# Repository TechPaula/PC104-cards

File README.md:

# PC104-cards

This is a place I will be putting various PCBs to go ontop of my PC104+ minicomputer.
No warranty for anything here, I add stuff as/when I feel like it and I can't promise what is here works.

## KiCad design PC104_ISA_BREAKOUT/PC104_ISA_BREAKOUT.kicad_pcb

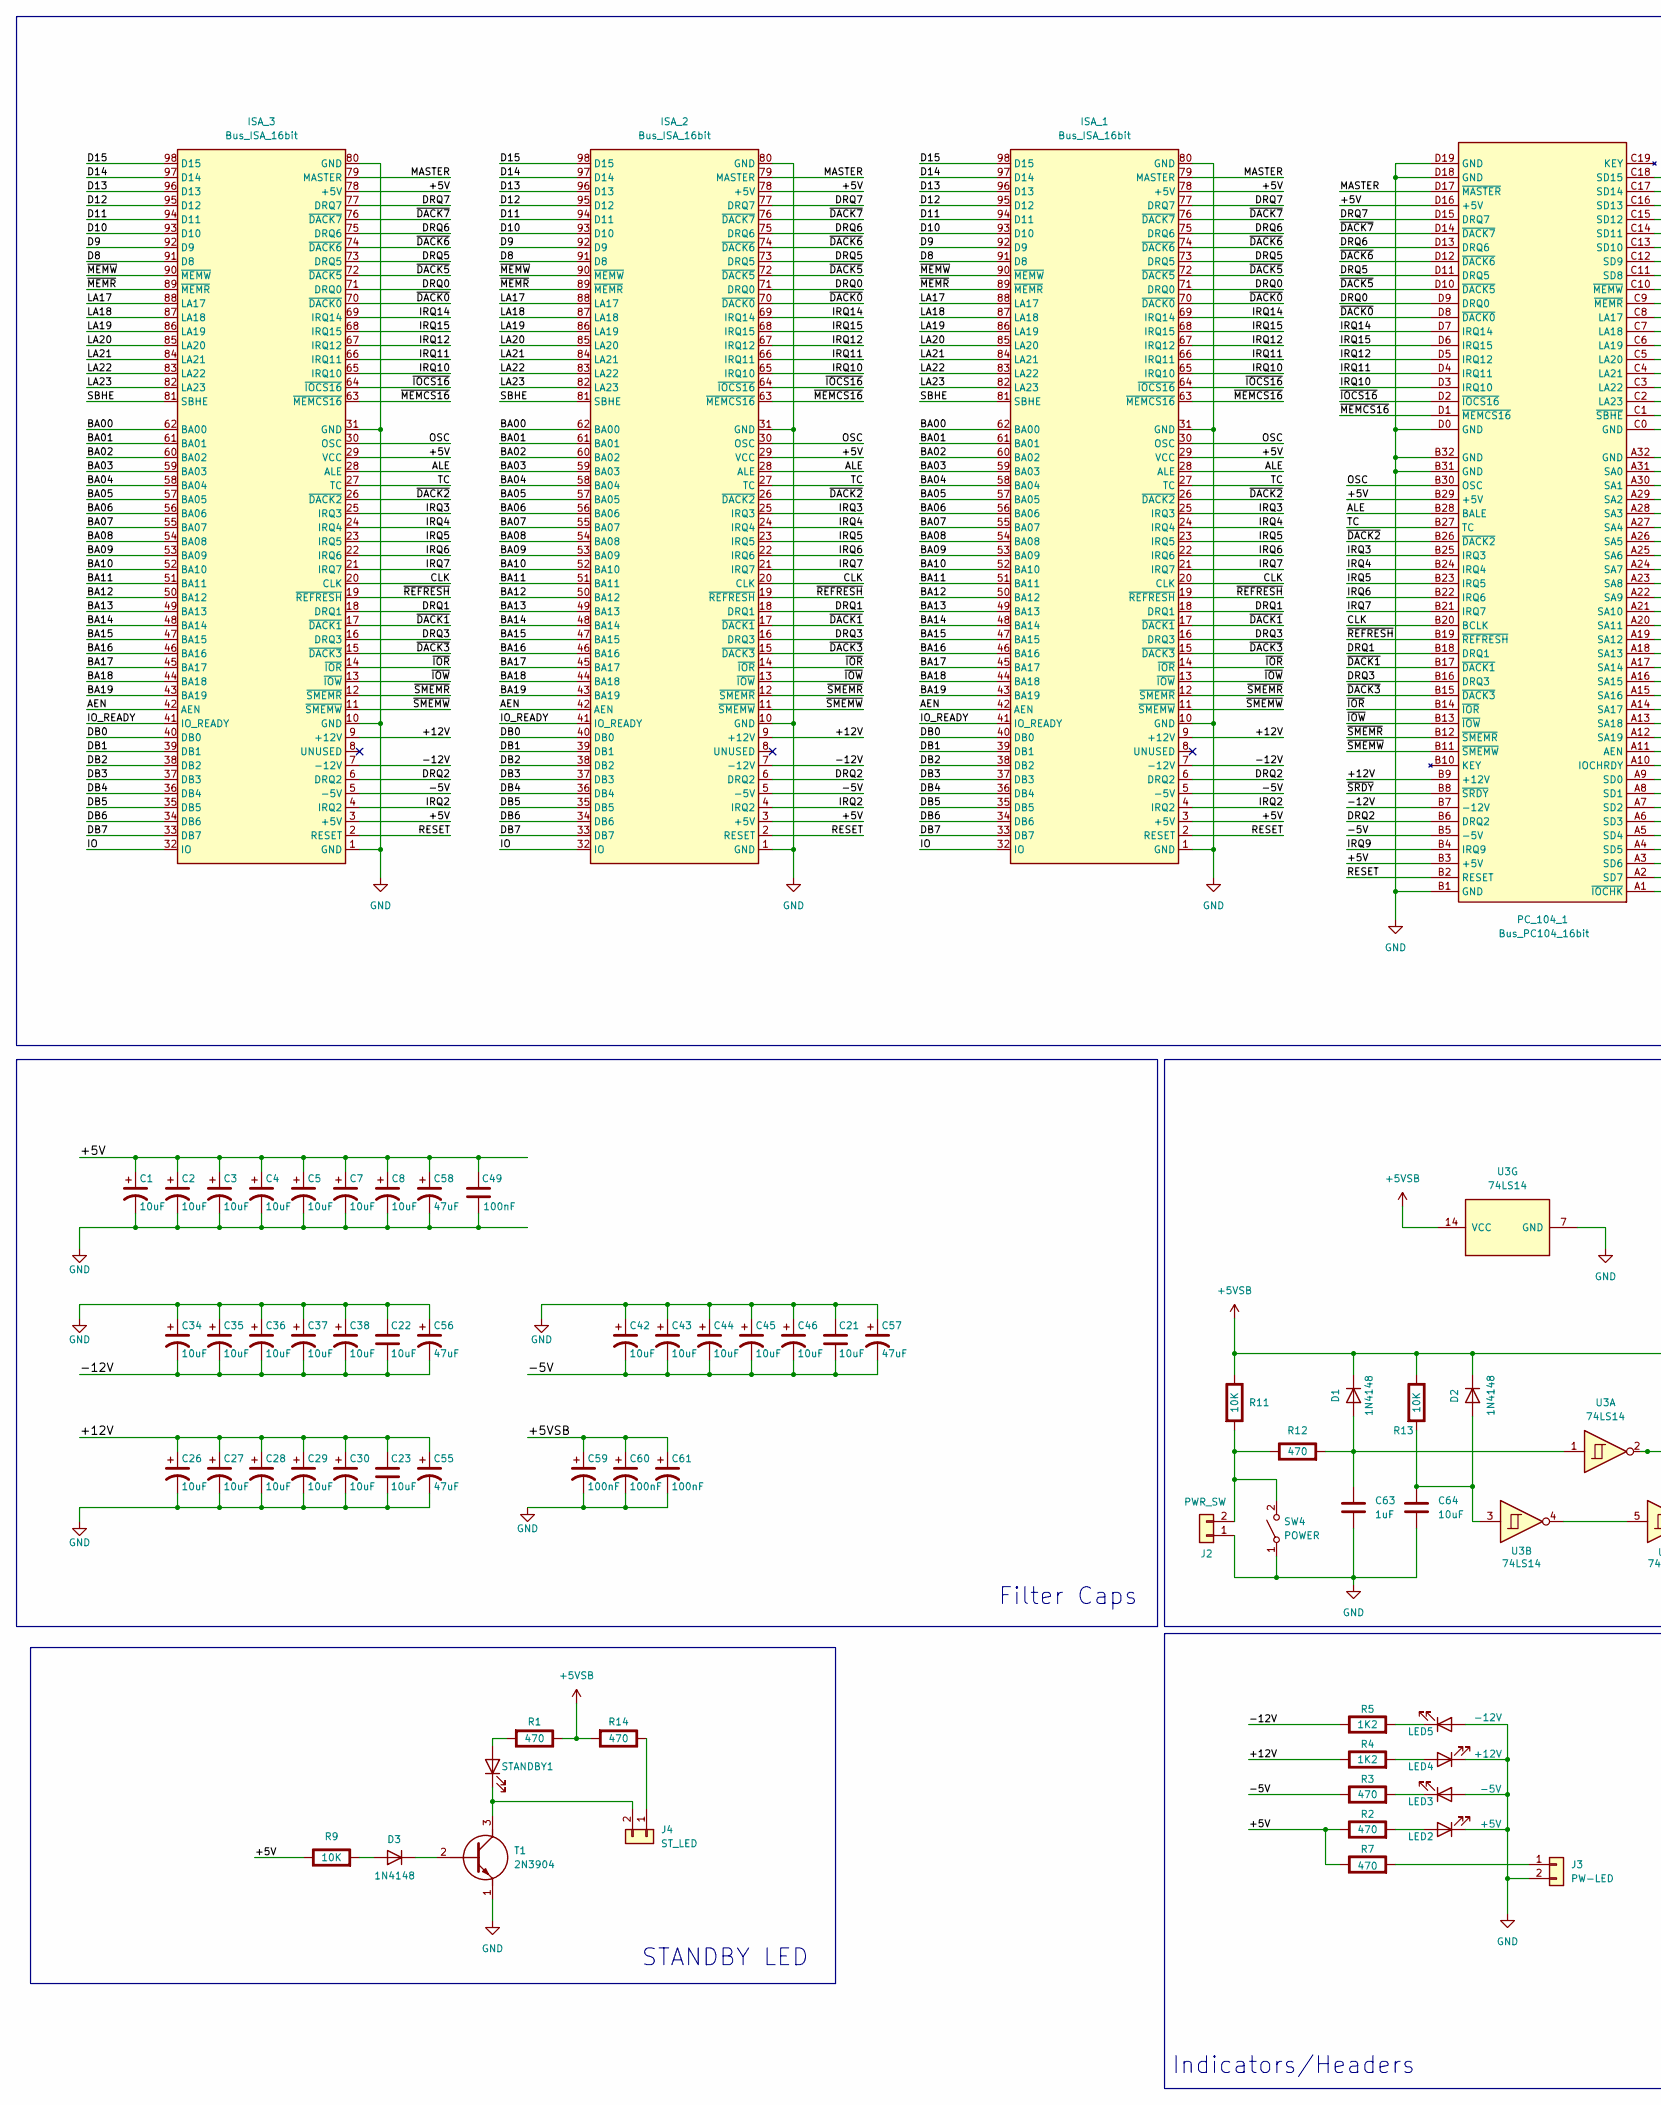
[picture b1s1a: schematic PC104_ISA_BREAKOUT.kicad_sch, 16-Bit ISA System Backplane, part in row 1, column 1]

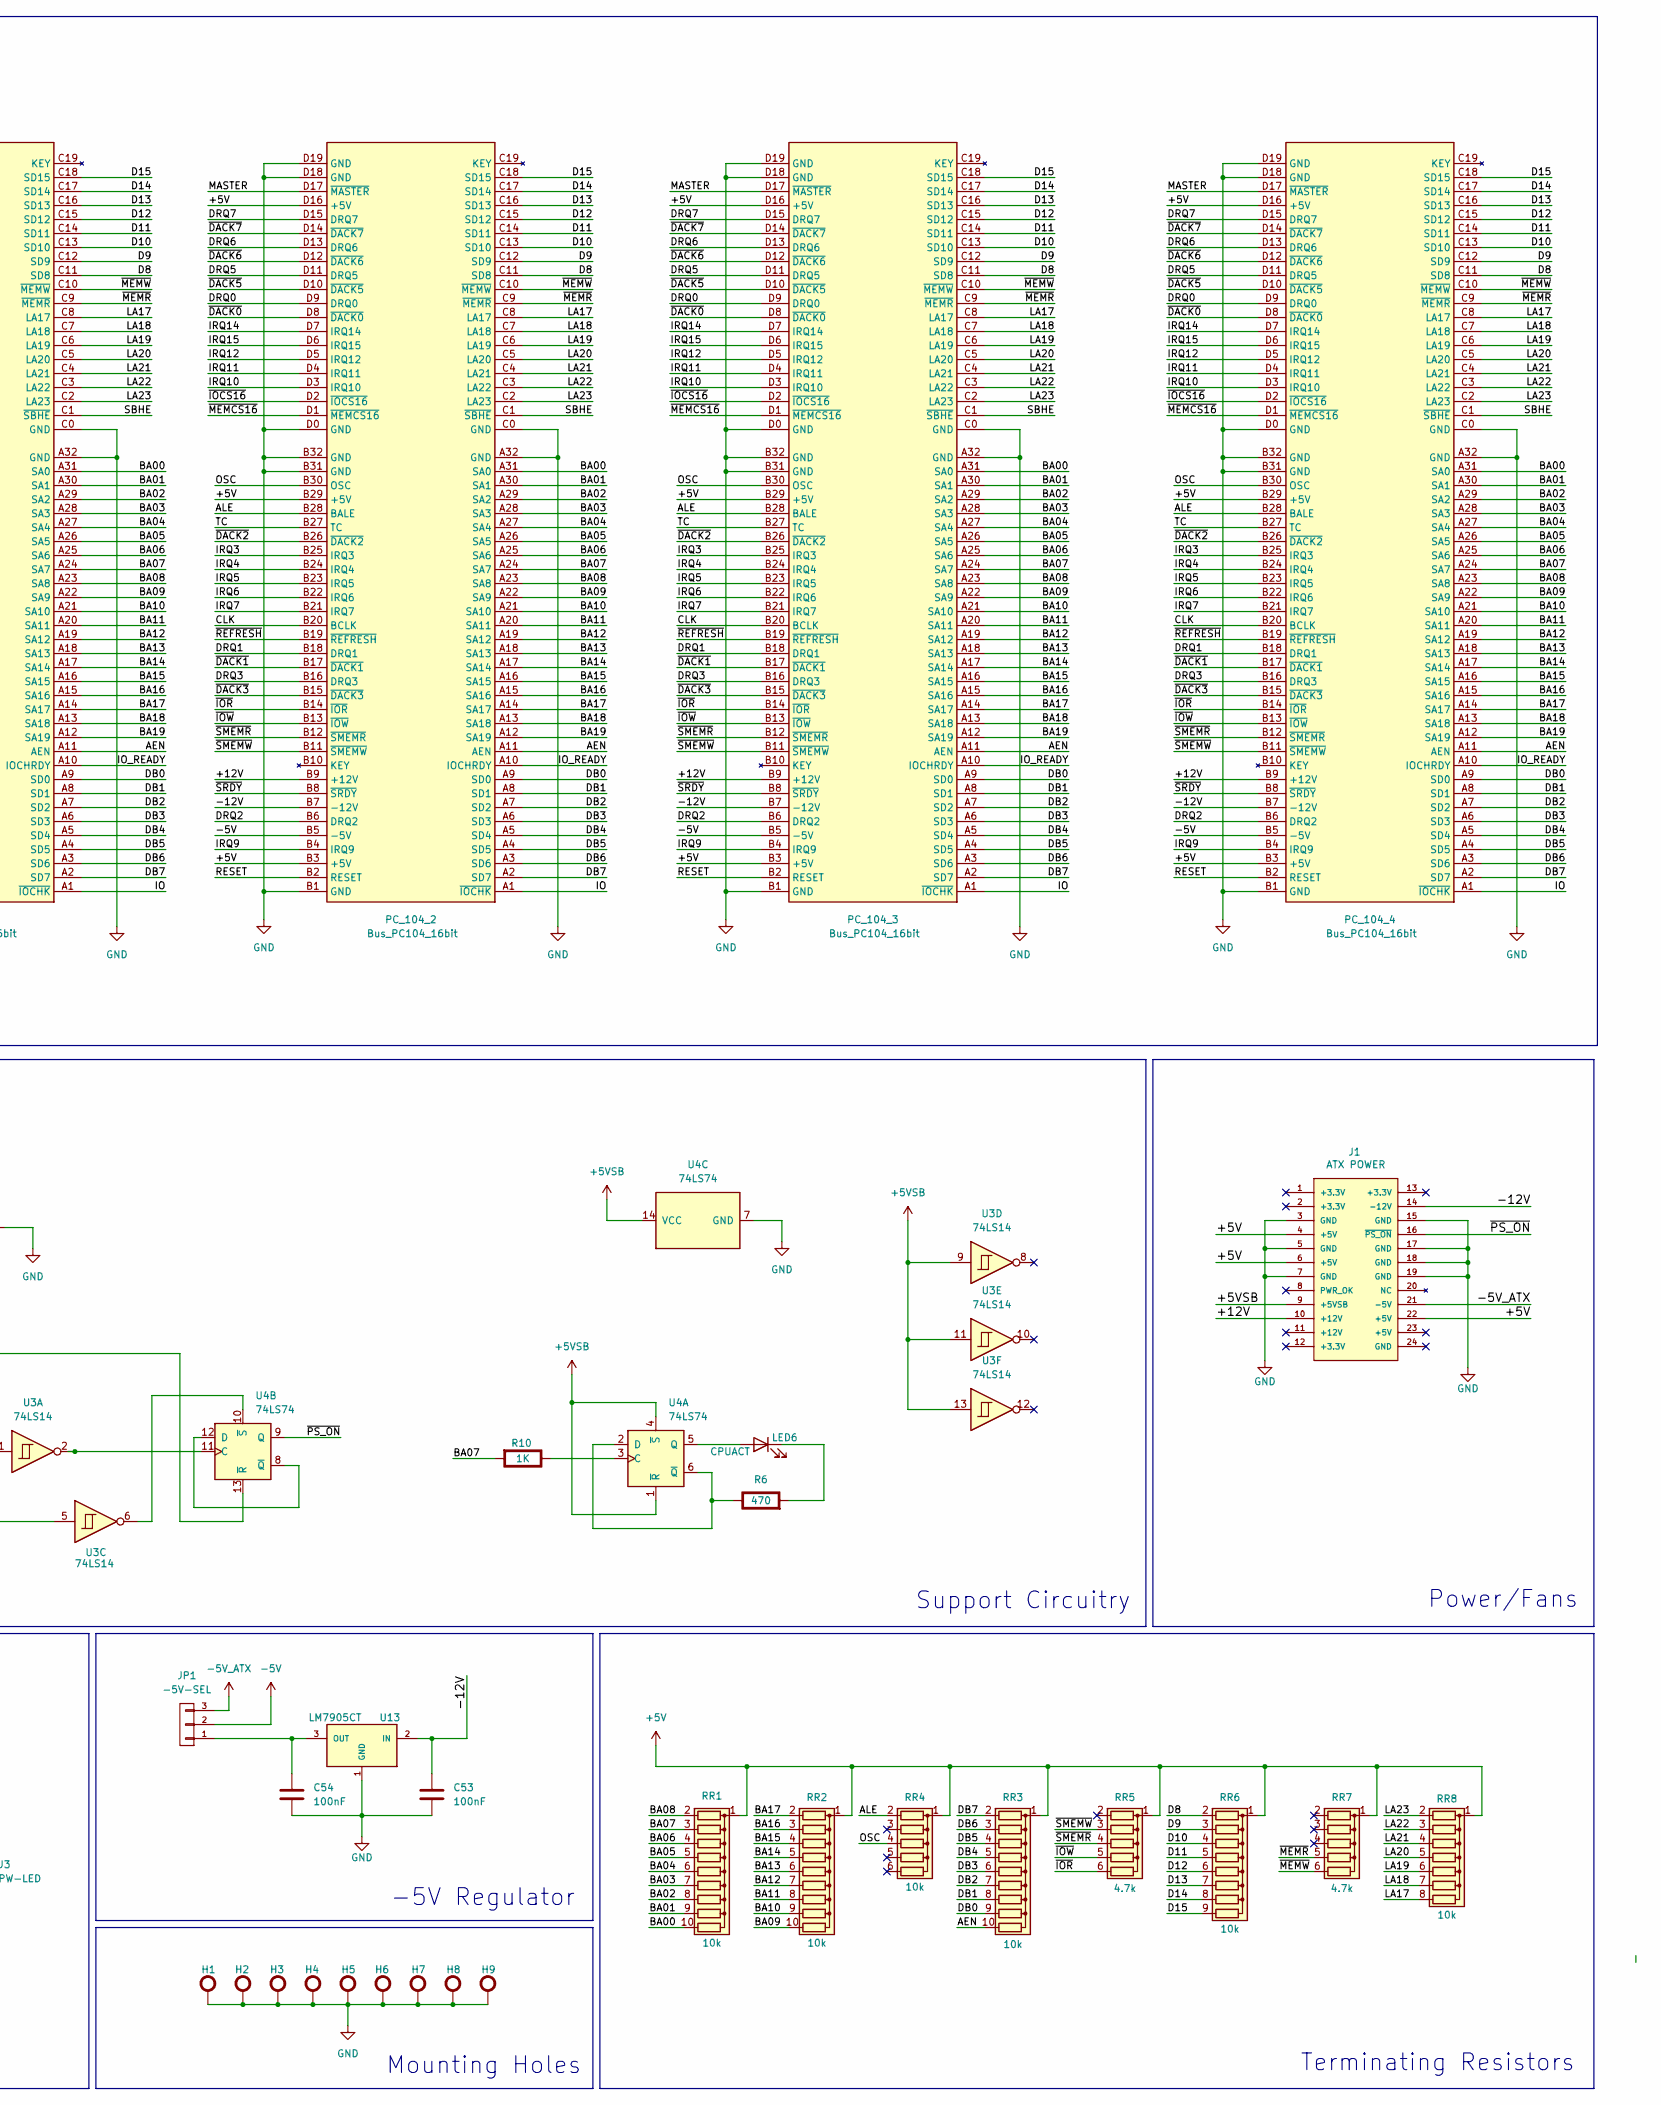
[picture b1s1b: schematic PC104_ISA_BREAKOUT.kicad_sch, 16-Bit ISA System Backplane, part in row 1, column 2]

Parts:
C1, C2, C3, C4, C5, C7, C8, C21, C22, C23, C26, C27, C28, C29, C30, C34, C35, C36, C37, C38, C42, C43, C44, C45, C46, C64: 10uF; C_1206_3216Metric
C49, C53, C54, C59, C60, C61: 100nF; C_0805_2012Metric
C55, C56, C57, C58: 47uF; C_1206_3216Metric
C63: 1uF; C_0805_2012Metric
D1, D2, D3: 1N4148; DIOAD990W55L340D162
H1, H2, H3, H4, H5, H6, H7, H8, H9: H_HOLE; MountingHole_4.3mm_M4_Pad_Via
ISA_1, ISA_2, ISA_3: Bus_ISA_16bit; BP_ISA_16BIT_SQ
J1: ATX POWER; J_ATX_5.5mm
J2: PWR_SW; P_CONN_01X02
J3: PW-LED; P_CONN_01X02
J4: ST_LED; P_CONN_01X02
JP1: -5V-SEL; P_CONN_01X03
LED2: +5V; LED_D5.0mm
LED3: -5V; LED_D5.0mm
LED4: +12V; LED_D5.0mm
LED5: -12V; LED_D5.0mm
LED6: CPUACT; LED_D5.0mm
PC_104_1, PC_104_2, PC_104_3, PC_104_4: Bus_PC104_16bit; PC104_BOARD
R1, R2, R3, R6, R7, R12, R14: 470; R_0805_2012Metric; Rating W
R4, R5: 1K2; R_0805_2012Metric; Rating W
R9, R11, R13: 10K; R_0805_2012Metric; Rating W
R10: 1K; R_0805_2012Metric; Rating W
RR1, RR2, RR3: 10k; R_Array_SIP10
RR4: 10k; R_Array_SIP6
RR5, RR7: 4.7k; R_Array_SIP6
RR6: 10k; R_Array_SIP9
RR8: 10k; R_Array_SIP8
STANDBY1: STDBY; LED_D5.0mm
SW4: POWER; SW_B3FS-1010
T1: 2N3904; TO92127P495H495-3; Mouser Part Number 610-2N2222
U3: 74LS14; 1109931441001000
U4: 74LS74; 1109931441001000
U13: LM7905CT; SB_TO220

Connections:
+5V: C1.1, C2.1, C3.1, C4.1, C5.1, C7.1, C8.1, C49.1, C58.1, ISA_1.3 (+5V), ISA_1.29 (VCC), ISA_1.78 (+5V), ISA_2.3 (+5V), ISA_2.29 (VCC), ISA_2.78 (+5V), ISA_3.3 (+5V), ISA_3.29 (VCC), ISA_3.78 (+5V), J1.4 (+5V), J1.6 (+5V), J1.22 (+5V), PC_104_1.B3 (+5V), PC_104_1.B29 (+5V), PC_104_1.D16 (+5V), PC_104_2.B3 (+5V), PC_104_2.B29 (+5V), PC_104_2.D16 (+5V), PC_104_3.B3 (+5V), PC_104_3.B29 (+5V), PC_104_3.D16 (+5V), PC_104_4.B3 (+5V), PC_104_4.B29 (+5V), PC_104_4.D16 (+5V), R2.1 (+), R7.1 (+), R9.1 (+), RR1.1 (common), RR2.1 (common), RR3.1 (common), RR4.1 (common), RR5.1 (common), RR6.1 (common), RR7.1 (common), RR8.1 (common)
+5VSB: C59.1, C60.1, C61.1, D1.1 (K), D2.1 (K), J1.9 (+5VSB), R1.1 (+), R11.1 (+), R13.1 (+), R14.2 (-), U3.9, U3.11, U3.13, U3.14 (VCC), U4.1 (~R), U4.4 (~S), U4.13 (~R), U4.14 (VCC)
-5V: C21.2, C42.2, C43.2, C44.2, C45.2, C46.2, C57.2, ISA_1.5 (-5V), ISA_2.5 (-5V), ISA_3.5 (-5V), JP1.2, PC_104_1.B5 (-5V), PC_104_2.B5 (-5V), PC_104_3.B5 (-5V), PC_104_4.B5 (-5V), R3.1 (+)
-5V_ATX: J1.21 (-5V), JP1.3
/+12V: C23.1, C26.1, C27.1, C28.1, C29.1, C30.1, C55.1, ISA_1.9 (+12V), ISA_2.9 (+12V), ISA_3.9 (+12V), J1.10 (+12V), PC_104_1.B9 (+12V), PC_104_2.B9 (+12V), PC_104_3.B9 (+12V), PC_104_4.B9 (+12V), R4.1 (+)
/-12V: C22.2, C34.2, C35.2, C36.2, C37.2, C38.2, C53.1, C56.2, ISA_1.7 (-12V), ISA_2.7 (-12V), ISA_3.7 (-12V), J1.14 (-12V), PC_104_1.B7 (-12V), PC_104_2.B7 (-12V), PC_104_3.B7 (-12V), PC_104_4.B7 (-12V), R5.1 (+), U13.2 (IN)
/AEN: ISA_1.42 (AEN), ISA_2.42 (AEN), ISA_3.42 (AEN), PC_104_1.A11 (AEN), PC_104_2.A11 (AEN), PC_104_3.A11 (AEN), PC_104_4.A11 (AEN), RR3.10 (R9)
/ALE: ISA_1.28 (ALE), ISA_2.28 (ALE), ISA_3.28 (ALE), PC_104_1.B28 (BALE), PC_104_2.B28 (BALE), PC_104_3.B28 (BALE), PC_104_4.B28 (BALE), RR4.2 (R1)
/BA00: ISA_1.62 (BA00), ISA_2.62 (BA00), ISA_3.62 (BA00), PC_104_1.A31 (SA0), PC_104_2.A31 (SA0), PC_104_3.A31 (SA0), PC_104_4.A31 (SA0), RR1.10 (R9)
/BA01: ISA_1.61 (BA01), ISA_2.61 (BA01), ISA_3.61 (BA01), PC_104_1.A30 (SA1), PC_104_2.A30 (SA1), PC_104_3.A30 (SA1), PC_104_4.A30 (SA1), RR1.9 (R8)
/BA02: ISA_1.60 (BA02), ISA_2.60 (BA02), ISA_3.60 (BA02), PC_104_1.A29 (SA2), PC_104_2.A29 (SA2), PC_104_3.A29 (SA2), PC_104_4.A29 (SA2), RR1.8 (R7)
/BA03: ISA_1.59 (BA03), ISA_2.59 (BA03), ISA_3.59 (BA03), PC_104_1.A28 (SA3), PC_104_2.A28 (SA3), PC_104_3.A28 (SA3), PC_104_4.A28 (SA3), RR1.7 (R6)
/BA04: ISA_1.58 (BA04), ISA_2.58 (BA04), ISA_3.58 (BA04), PC_104_1.A27 (SA4), PC_104_2.A27 (SA4), PC_104_3.A27 (SA4), PC_104_4.A27 (SA4), RR1.6 (R5)
/BA05: ISA_1.57 (BA05), ISA_2.57 (BA05), ISA_3.57 (BA05), PC_104_1.A26 (SA5), PC_104_2.A26 (SA5), PC_104_3.A26 (SA5), PC_104_4.A26 (SA5), RR1.5 (R4)
/BA06: ISA_1.56 (BA06), ISA_2.56 (BA06), ISA_3.56 (BA06), PC_104_1.A25 (SA6), PC_104_2.A25 (SA6), PC_104_3.A25 (SA6), PC_104_4.A25 (SA6), RR1.4 (R3)
/BA07: ISA_1.55 (BA07), ISA_2.55 (BA07), ISA_3.55 (BA07), PC_104_1.A24 (SA7), PC_104_2.A24 (SA7), PC_104_3.A24 (SA7), PC_104_4.A24 (SA7), R10.2 (-), RR1.3 (R2)
/BA08: ISA_1.54 (BA08), ISA_2.54 (BA08), ISA_3.54 (BA08), PC_104_1.A23 (SA8), PC_104_2.A23 (SA8), PC_104_3.A23 (SA8), PC_104_4.A23 (SA8), RR1.2 (R1)
/BA09: ISA_1.53 (BA09), ISA_2.53 (BA09), ISA_3.53 (BA09), PC_104_1.A22 (SA9), PC_104_2.A22 (SA9), PC_104_3.A22 (SA9), PC_104_4.A22 (SA9), RR2.10 (R9)
/BA10: ISA_1.52 (BA10), ISA_2.52 (BA10), ISA_3.52 (BA10), PC_104_1.A21 (SA10), PC_104_2.A21 (SA10), PC_104_3.A21 (SA10), PC_104_4.A21 (SA10), RR2.9 (R8)
/BA11: ISA_1.51 (BA11), ISA_2.51 (BA11), ISA_3.51 (BA11), PC_104_1.A20 (SA11), PC_104_2.A20 (SA11), PC_104_3.A20 (SA11), PC_104_4.A20 (SA11), RR2.8 (R7)
/BA12: ISA_1.50 (BA12), ISA_2.50 (BA12), ISA_3.50 (BA12), PC_104_1.A19 (SA12), PC_104_2.A19 (SA12), PC_104_3.A19 (SA12), PC_104_4.A19 (SA12), RR2.7 (R6)
/BA13: ISA_1.49 (BA13), ISA_2.49 (BA13), ISA_3.49 (BA13), PC_104_1.A18 (SA13), PC_104_2.A18 (SA13), PC_104_3.A18 (SA13), PC_104_4.A18 (SA13), RR2.6 (R5)
/BA14: ISA_1.48 (BA14), ISA_2.48 (BA14), ISA_3.48 (BA14), PC_104_1.A17 (SA14), PC_104_2.A17 (SA14), PC_104_3.A17 (SA14), PC_104_4.A17 (SA14), RR2.5 (R4)
/BA15: ISA_1.47 (BA15), ISA_2.47 (BA15), ISA_3.47 (BA15), PC_104_1.A16 (SA15), PC_104_2.A16 (SA15), PC_104_3.A16 (SA15), PC_104_4.A16 (SA15), RR2.4 (R3)
/BA16: ISA_1.46 (BA16), ISA_2.46 (BA16), ISA_3.46 (BA16), PC_104_1.A15 (SA16), PC_104_2.A15 (SA16), PC_104_3.A15 (SA16), PC_104_4.A15 (SA16), RR2.3 (R2)
/BA17: ISA_1.45 (BA17), ISA_2.45 (BA17), ISA_3.45 (BA17), PC_104_1.A14 (SA17), PC_104_2.A14 (SA17), PC_104_3.A14 (SA17), PC_104_4.A14 (SA17), RR2.2 (R1)
/BA18: ISA_1.44 (BA18), ISA_2.44 (BA18), ISA_3.44 (BA18), PC_104_1.A13 (SA18), PC_104_2.A13 (SA18), PC_104_3.A13 (SA18), PC_104_4.A13 (SA18)
/BA19: ISA_1.43 (BA19), ISA_2.43 (BA19), ISA_3.43 (BA19), PC_104_1.A12 (SA19), PC_104_2.A12 (SA19), PC_104_3.A12 (SA19), PC_104_4.A12 (SA19)
/CLK: ISA_1.20 (CLK), ISA_2.20 (CLK), ISA_3.20 (CLK), PC_104_1.B20 (BCLK), PC_104_2.B20 (BCLK), PC_104_3.B20 (BCLK), PC_104_4.B20 (BCLK)
/D8: ISA_1.91 (D8), ISA_2.91 (D8), ISA_3.91 (D8), PC_104_1.C11 (SD8), PC_104_2.C11 (SD8), PC_104_3.C11 (SD8), PC_104_4.C11 (SD8), RR6.2 (R1)
/D9: ISA_1.92 (D9), ISA_2.92 (D9), ISA_3.92 (D9), PC_104_1.C12 (SD9), PC_104_2.C12 (SD9), PC_104_3.C12 (SD9), PC_104_4.C12 (SD9), RR6.3 (R2)
/D10: ISA_1.93 (D10), ISA_2.93 (D10), ISA_3.93 (D10), PC_104_1.C13 (SD10), PC_104_2.C13 (SD10), PC_104_3.C13 (SD10), PC_104_4.C13 (SD10), RR6.4 (R3)
/D11: ISA_1.94 (D11), ISA_2.94 (D11), ISA_3.94 (D11), PC_104_1.C14 (SD11), PC_104_2.C14 (SD11), PC_104_3.C14 (SD11), PC_104_4.C14 (SD11), RR6.5 (R4)
/D12: ISA_1.95 (D12), ISA_2.95 (D12), ISA_3.95 (D12), PC_104_1.C15 (SD12), PC_104_2.C15 (SD12), PC_104_3.C15 (SD12), PC_104_4.C15 (SD12), RR6.6 (R5)
/D13: ISA_1.96 (D13), ISA_2.96 (D13), ISA_3.96 (D13), PC_104_1.C16 (SD13), PC_104_2.C16 (SD13), PC_104_3.C16 (SD13), PC_104_4.C16 (SD13), RR6.7 (R6)
/D14: ISA_1.97 (D14), ISA_2.97 (D14), ISA_3.97 (D14), PC_104_1.C17 (SD14), PC_104_2.C17 (SD14), PC_104_3.C17 (SD14), PC_104_4.C17 (SD14), RR6.8 (R7)
/D15: ISA_1.98 (D15), ISA_2.98 (D15), ISA_3.98 (D15), PC_104_1.C18 (SD15), PC_104_2.C18 (SD15), PC_104_3.C18 (SD15), PC_104_4.C18 (SD15), RR6.9 (R8)
/DB0: ISA_1.40 (DB0), ISA_2.40 (DB0), ISA_3.40 (DB0), PC_104_1.A9 (SD0), PC_104_2.A9 (SD0), PC_104_3.A9 (SD0), PC_104_4.A9 (SD0), RR3.9 (R8)
/DB1: ISA_1.39 (DB1), ISA_2.39 (DB1), ISA_3.39 (DB1), PC_104_1.A8 (SD1), PC_104_2.A8 (SD1), PC_104_3.A8 (SD1), PC_104_4.A8 (SD1), RR3.8 (R7)
/DB2: ISA_1.38 (DB2), ISA_2.38 (DB2), ISA_3.38 (DB2), PC_104_1.A7 (SD2), PC_104_2.A7 (SD2), PC_104_3.A7 (SD2), PC_104_4.A7 (SD2), RR3.7 (R6)
/DB3: ISA_1.37 (DB3), ISA_2.37 (DB3), ISA_3.37 (DB3), PC_104_1.A6 (SD3), PC_104_2.A6 (SD3), PC_104_3.A6 (SD3), PC_104_4.A6 (SD3), RR3.6 (R5)
/DB4: ISA_1.36 (DB4), ISA_2.36 (DB4), ISA_3.36 (DB4), PC_104_1.A5 (SD4), PC_104_2.A5 (SD4), PC_104_3.A5 (SD4), PC_104_4.A5 (SD4), RR3.5 (R4)
/DB5: ISA_1.35 (DB5), ISA_2.35 (DB5), ISA_3.35 (DB5), PC_104_1.A4 (SD5), PC_104_2.A4 (SD5), PC_104_3.A4 (SD5), PC_104_4.A4 (SD5), RR3.4 (R3)
/DB6: ISA_1.34 (DB6), ISA_2.34 (DB6), ISA_3.34 (DB6), PC_104_1.A3 (SD6), PC_104_2.A3 (SD6), PC_104_3.A3 (SD6), PC_104_4.A3 (SD6), RR3.3 (R2)
/DB7: ISA_1.33 (DB7), ISA_2.33 (DB7), ISA_3.33 (DB7), PC_104_1.A2 (SD7), PC_104_2.A2 (SD7), PC_104_3.A2 (SD7), PC_104_4.A2 (SD7), RR3.2 (R1)
/DRQ0: ISA_1.71 (DRQ0), ISA_2.71 (DRQ0), ISA_3.71 (DRQ0), PC_104_1.D9 (DRQ0), PC_104_2.D9 (DRQ0), PC_104_3.D9 (DRQ0), PC_104_4.D9 (DRQ0)
/DRQ1: ISA_1.18 (DRQ1), ISA_2.18 (DRQ1), ISA_3.18 (DRQ1), PC_104_1.B18 (DRQ1), PC_104_2.B18 (DRQ1), PC_104_3.B18 (DRQ1), PC_104_4.B18 (DRQ1)
/DRQ2: ISA_1.6 (DRQ2), ISA_2.6 (DRQ2), ISA_3.6 (DRQ2), PC_104_1.B6 (DRQ2), PC_104_2.B6 (DRQ2), PC_104_3.B6 (DRQ2), PC_104_4.B6 (DRQ2)
/DRQ3: ISA_1.16 (DRQ3), ISA_2.16 (DRQ3), ISA_3.16 (DRQ3), PC_104_1.B16 (DRQ3), PC_104_2.B16 (DRQ3), PC_104_3.B16 (DRQ3), PC_104_4.B16 (DRQ3)
/DRQ5: ISA_1.73 (DRQ5), ISA_2.73 (DRQ5), ISA_3.73 (DRQ5), PC_104_1.D11 (DRQ5), PC_104_2.D11 (DRQ5), PC_104_3.D11 (DRQ5), PC_104_4.D11 (DRQ5)
/DRQ6: ISA_1.75 (DRQ6), ISA_2.75 (DRQ6), ISA_3.75 (DRQ6), PC_104_1.D13 (DRQ6), PC_104_2.D13 (DRQ6), PC_104_3.D13 (DRQ6), PC_104_4.D13 (DRQ6)
/DRQ7: ISA_1.77 (DRQ7), ISA_2.77 (DRQ7), ISA_3.77 (DRQ7), PC_104_1.D15 (DRQ7), PC_104_2.D15 (DRQ7), PC_104_3.D15 (DRQ7), PC_104_4.D15 (DRQ7)
/IO: ISA_1.32 (IO), ISA_2.32 (IO), ISA_3.32 (IO), PC_104_1.A1 (~IOCHK), PC_104_2.A1 (~IOCHK), PC_104_3.A1 (~IOCHK), PC_104_4.A1 (~IOCHK)
/IO_READY: ISA_1.41 (IO_READY), ISA_2.41 (IO_READY), ISA_3.41 (IO_READY), PC_104_1.A10 (IOCHRDY), PC_104_2.A10 (IOCHRDY), PC_104_3.A10 (IOCHRDY), PC_104_4.A10 (IOCHRDY)
/IRQ2: ISA_1.4 (IRQ2), ISA_2.4 (IRQ2), ISA_3.4 (IRQ2)
/IRQ3: ISA_1.25 (IRQ3), ISA_2.25 (IRQ3), ISA_3.25 (IRQ3), PC_104_1.B25 (IRQ3), PC_104_2.B25 (IRQ3), PC_104_3.B25 (IRQ3), PC_104_4.B25 (IRQ3)
/IRQ4: ISA_1.24 (IRQ4), ISA_2.24 (IRQ4), ISA_3.24 (IRQ4), PC_104_1.B24 (IRQ4), PC_104_2.B24 (IRQ4), PC_104_3.B24 (IRQ4), PC_104_4.B24 (IRQ4)
/IRQ5: ISA_1.23 (IRQ5), ISA_2.23 (IRQ5), ISA_3.23 (IRQ5), PC_104_1.B23 (IRQ5), PC_104_2.B23 (IRQ5), PC_104_3.B23 (IRQ5), PC_104_4.B23 (IRQ5)
/IRQ6: ISA_1.22 (IRQ6), ISA_2.22 (IRQ6), ISA_3.22 (IRQ6), PC_104_1.B22 (IRQ6), PC_104_2.B22 (IRQ6), PC_104_3.B22 (IRQ6), PC_104_4.B22 (IRQ6)
/IRQ7: ISA_1.21 (IRQ7), ISA_2.21 (IRQ7), ISA_3.21 (IRQ7), PC_104_1.B21 (IRQ7), PC_104_2.B21 (IRQ7), PC_104_3.B21 (IRQ7), PC_104_4.B21 (IRQ7)
/IRQ9: PC_104_1.B4 (IRQ9), PC_104_2.B4 (IRQ9), PC_104_3.B4 (IRQ9), PC_104_4.B4 (IRQ9)
/IRQ10: ISA_1.65 (IRQ10), ISA_2.65 (IRQ10), ISA_3.65 (IRQ10), PC_104_1.D3 (IRQ10), PC_104_2.D3 (IRQ10), PC_104_3.D3 (IRQ10), PC_104_4.D3 (IRQ10)
/IRQ11: ISA_1.66 (IRQ11), ISA_2.66 (IRQ11), ISA_3.66 (IRQ11), PC_104_1.D4 (IRQ11), PC_104_2.D4 (IRQ11), PC_104_3.D4 (IRQ11), PC_104_4.D4 (IRQ11)
/IRQ12: ISA_1.67 (IRQ12), ISA_2.67 (IRQ12), ISA_3.67 (IRQ12), PC_104_1.D5 (IRQ12), PC_104_2.D5 (IRQ12), PC_104_3.D5 (IRQ12), PC_104_4.D5 (IRQ12)
/IRQ14: ISA_1.69 (IRQ14), ISA_2.69 (IRQ14), ISA_3.69 (IRQ14), PC_104_1.D7 (IRQ14), PC_104_2.D7 (IRQ14), PC_104_3.D7 (IRQ14), PC_104_4.D7 (IRQ14)
/IRQ15: ISA_1.68 (IRQ15), ISA_2.68 (IRQ15), ISA_3.68 (IRQ15), PC_104_1.D6 (IRQ15), PC_104_2.D6 (IRQ15), PC_104_3.D6 (IRQ15), PC_104_4.D6 (IRQ15)
/LA17: ISA_1.88 (LA17), ISA_2.88 (LA17), ISA_3.88 (LA17), PC_104_1.C8 (LA17), PC_104_2.C8 (LA17), PC_104_3.C8 (LA17), PC_104_4.C8 (LA17), RR8.8 (R7)
/LA18: ISA_1.87 (LA18), ISA_2.87 (LA18), ISA_3.87 (LA18), PC_104_1.C7 (LA18), PC_104_2.C7 (LA18), PC_104_3.C7 (LA18), PC_104_4.C7 (LA18), RR8.7 (R6)
/LA19: ISA_1.86 (LA19), ISA_2.86 (LA19), ISA_3.86 (LA19), PC_104_1.C6 (LA19), PC_104_2.C6 (LA19), PC_104_3.C6 (LA19), PC_104_4.C6 (LA19), RR8.6 (R5)
/LA20: ISA_1.85 (LA20), ISA_2.85 (LA20), ISA_3.85 (LA20), PC_104_1.C5 (LA20), PC_104_2.C5 (LA20), PC_104_3.C5 (LA20), PC_104_4.C5 (LA20), RR8.5 (R4)
/LA21: ISA_1.84 (LA21), ISA_2.84 (LA21), ISA_3.84 (LA21), PC_104_1.C4 (LA21), PC_104_2.C4 (LA21), PC_104_3.C4 (LA21), PC_104_4.C4 (LA21), RR8.4 (R3)
/LA22: ISA_1.83 (LA22), ISA_2.83 (LA22), ISA_3.83 (LA22), PC_104_1.C3 (LA22), PC_104_2.C3 (LA22), PC_104_3.C3 (LA22), PC_104_4.C3 (LA22), RR8.3 (R2)
/LA23: ISA_1.82 (LA23), ISA_2.82 (LA23), ISA_3.82 (LA23), PC_104_1.C2 (LA23), PC_104_2.C2 (LA23), PC_104_3.C2 (LA23), PC_104_4.C2 (LA23), RR8.2 (R1)
/MASTER: ISA_1.79 (MASTER), ISA_2.79 (MASTER), ISA_3.79 (MASTER), PC_104_1.D17 (~MASTER), PC_104_2.D17 (~MASTER), PC_104_3.D17 (~MASTER), PC_104_4.D17 (~MASTER)
/OSC: ISA_1.30 (OSC), ISA_2.30 (OSC), ISA_3.30 (OSC), PC_104_1.B30 (OSC), PC_104_2.B30 (OSC), PC_104_3.B30 (OSC), PC_104_4.B30 (OSC), RR4.4 (R3)
/RESET: ISA_1.2 (RESET), ISA_2.2 (RESET), ISA_3.2 (RESET), PC_104_1.B2 (RESET), PC_104_2.B2 (RESET), PC_104_3.B2 (RESET), PC_104_4.B2 (RESET)
/SBHE: ISA_1.81 (SBHE), ISA_2.81 (SBHE), ISA_3.81 (SBHE), PC_104_1.C1 (~SBHE), PC_104_2.C1 (~SBHE), PC_104_3.C1 (~SBHE), PC_104_4.C1 (~SBHE)
/TC: ISA_1.27 (TC), ISA_2.27 (TC), ISA_3.27 (TC), PC_104_1.B27 (TC), PC_104_2.B27 (TC), PC_104_3.B27 (TC), PC_104_4.B27 (TC)
/~DACK0: ISA_1.70 (~DACK0), ISA_2.70 (~DACK0), ISA_3.70 (~DACK0), PC_104_1.D8 (~DACK0), PC_104_2.D8 (~DACK0), PC_104_3.D8 (~DACK0), PC_104_4.D8 (~DACK0)
/~DACK1: ISA_1.17 (~DACK1), ISA_2.17 (~DACK1), ISA_3.17 (~DACK1), PC_104_1.B17 (~DACK1), PC_104_2.B17 (~DACK1), PC_104_3.B17 (~DACK1), PC_104_4.B17 (~DACK1)
/~DACK2: ISA_1.26 (~DACK2), ISA_2.26 (~DACK2), ISA_3.26 (~DACK2), PC_104_1.B26 (~DACK2), PC_104_2.B26 (~DACK2), PC_104_3.B26 (~DACK2), PC_104_4.B26 (~DACK2)
/~DACK3: ISA_1.15 (~DACK3), ISA_2.15 (~DACK3), ISA_3.15 (~DACK3), PC_104_1.B15 (~DACK3), PC_104_2.B15 (~DACK3), PC_104_3.B15 (~DACK3), PC_104_4.B15 (~DACK3)
/~DACK5: ISA_1.72 (~DACK5), ISA_2.72 (~DACK5), ISA_3.72 (~DACK5), PC_104_1.D10 (~DACK5), PC_104_2.D10 (~DACK5), PC_104_3.D10 (~DACK5), PC_104_4.D10 (~DACK5)
/~DACK6: ISA_1.74 (~DACK6), ISA_2.74 (~DACK6), ISA_3.74 (~DACK6), PC_104_1.D12 (~DACK6), PC_104_2.D12 (~DACK6), PC_104_3.D12 (~DACK6), PC_104_4.D12 (~DACK6)
/~DACK7: ISA_1.76 (~DACK7), ISA_2.76 (~DACK7), ISA_3.76 (~DACK7), PC_104_1.D14 (~DACK7), PC_104_2.D14 (~DACK7), PC_104_3.D14 (~DACK7), PC_104_4.D14 (~DACK7)
/~IOCS16: ISA_1.64 (~IOCS16), ISA_2.64 (~IOCS16), ISA_3.64 (~IOCS16), PC_104_1.D2 (~IOCS16), PC_104_2.D2 (~IOCS16), PC_104_3.D2 (~IOCS16), PC_104_4.D2 (~IOCS16)
/~IOR: ISA_1.14 (~IOR), ISA_2.14 (~IOR), ISA_3.14 (~IOR), PC_104_1.B14 (~IOR), PC_104_2.B14 (~IOR), PC_104_3.B14 (~IOR), PC_104_4.B14 (~IOR), RR5.6 (R5)
/~IOW: ISA_1.13 (~IOW), ISA_2.13 (~IOW), ISA_3.13 (~IOW), PC_104_1.B13 (~IOW), PC_104_2.B13 (~IOW), PC_104_3.B13 (~IOW), PC_104_4.B13 (~IOW), RR5.5 (R4)
/~MEMCS16: ISA_1.63 (~MEMCS16), ISA_2.63 (~MEMCS16), ISA_3.63 (~MEMCS16), PC_104_1.D1 (~MEMCS16), PC_104_2.D1 (~MEMCS16), PC_104_3.D1 (~MEMCS16), PC_104_4.D1 (~MEMCS16)
/~MEMR: ISA_1.89 (~MEMR), ISA_2.89 (~MEMR), ISA_3.89 (~MEMR), PC_104_1.C9 (~MEMR), PC_104_2.C9 (~MEMR), PC_104_3.C9 (~MEMR), PC_104_4.C9 (~MEMR), RR7.5 (R4)
/~MEMW: ISA_1.90 (~MEMW), ISA_2.90 (~MEMW), ISA_3.90 (~MEMW), PC_104_1.C10 (~MEMW), PC_104_2.C10 (~MEMW), PC_104_3.C10 (~MEMW), PC_104_4.C10 (~MEMW), RR7.6 (R5)
/~PS_ON: J1.16 (~PS_ON), U4.9 (Q)
/~REFRESH: ISA_1.19 (~REFRESH), ISA_2.19 (~REFRESH), ISA_3.19 (~REFRESH), PC_104_1.B19 (~REFRESH), PC_104_2.B19 (~REFRESH), PC_104_3.B19 (~REFRESH), PC_104_4.B19 (~REFRESH)
/~SMEMR: ISA_1.12 (~SMEMR), ISA_2.12 (~SMEMR), ISA_3.12 (~SMEMR), PC_104_1.B12 (~SMEMR), PC_104_2.B12 (~SMEMR), PC_104_3.B12 (~SMEMR), PC_104_4.B12 (~SMEMR), RR5.4 (R3)
/~SMEMW: ISA_1.11 (~SMEMW), ISA_2.11 (~SMEMW), ISA_3.11 (~SMEMW), PC_104_1.B11 (~SMEMW), PC_104_2.B11 (~SMEMW), PC_104_3.B11 (~SMEMW), PC_104_4.B11 (~SMEMW), RR5.3 (R2)
/~SRDY: PC_104_1.B8 (~SRDY), PC_104_2.B8 (~SRDY), PC_104_3.B8 (~SRDY), PC_104_4.B8 (~SRDY)
GND: C1.2, C2.2, C3.2, C4.2, C5.2, C7.2, C8.2, C21.1, C22.1, C23.2, C26.2, C27.2, C28.2, C29.2, C30.2, C34.1, C35.1, C36.1, C37.1, C38.1, C42.1, C43.1, C44.1, C45.1, C46.1, C49.2, C53.2, C54.2, C55.2, C56.1, C57.1, C58.2, C59.2, C60.2, C61.2, C63.2, C64.2, H1.1, H2.1, H3.1, H4.1, H5.1, H6.1, H7.1, H8.1, H9.1, ISA_1.1 (GND), ISA_1.10 (GND), ISA_1.31 (GND), ISA_1.80 (GND), ISA_2.1 (GND), ISA_2.10 (GND), ISA_2.31 (GND), ISA_2.80 (GND), ISA_3.1 (GND), ISA_3.10 (GND), ISA_3.31 (GND), ISA_3.80 (GND), J1.3 (GND), J1.5 (GND), J1.7 (GND), J1.15 (GND), J1.17 (GND), J1.18 (GND), J1.19 (GND), J2.1, J3.2, LED2.1 (K), LED3.2 (A), LED4.1 (K), LED5.2 (A), PC_104_1.A32 (GND), PC_104_1.B1 (GND), PC_104_1.B31 (GND), PC_104_1.B32 (GND), PC_104_1.C0 (GND), PC_104_1.D0 (GND), PC_104_1.D18 (GND), PC_104_1.D19 (GND), PC_104_2.A32 (GND), PC_104_2.B1 (GND), PC_104_2.B31 (GND), PC_104_2.B32 (GND), PC_104_2.C0 (GND), PC_104_2.D0 (GND), PC_104_2.D18 (GND), PC_104_2.D19 (GND), PC_104_3.A32 (GND), PC_104_3.B1 (GND), PC_104_3.B31 (GND), PC_104_3.B32 (GND), PC_104_3.C0 (GND), PC_104_3.D0 (GND), PC_104_3.D18 (GND), PC_104_3.D19 (GND), PC_104_4.A32 (GND), PC_104_4.B1 (GND), PC_104_4.B31 (GND), PC_104_4.B32 (GND), PC_104_4.C0 (GND), PC_104_4.D0 (GND), PC_104_4.D18 (GND), PC_104_4.D19 (GND), SW4.1 (A), T1.1 (E), U3.7 (GND), U4.7 (GND), U13.1 (GND); also elsewhere on the board
unnamed: C63.1, D1.2 (A), R12.2 (-), U3.1
unnamed: C64.1, D2.2 (A), R13.2 (-), U3.3
unnamed: D3.2 (A), R9.2 (-)
unnamed: D3.1 (K), T1.2 (B)
unnamed: J2.2, R11.2 (-), R12.1 (+), SW4.2 (B)
unnamed: J3.1, R7.2 (-)
unnamed: J4.1, R14.1 (+)
unnamed: J4.2, STANDBY1.1 (K), T1.3 (C)
unnamed: LED2.2 (A), R2.2 (-)
unnamed: LED3.1 (K), R3.2 (-)
unnamed: LED4.2 (A), R4.2 (-)
unnamed: LED5.1 (K), R5.2 (-)
unnamed: LED6.2 (A), U4.5 (Q)
unnamed: LED6.1 (K), R6.2 (-)
unnamed: R1.2 (-), STANDBY1.2 (A)
unnamed: R6.1 (+), U4.2 (D), U4.6 (~Q)
unnamed: R10.1 (+), U4.3 (C)
unnamed: U3.4, U3.5
unnamed: U3.2, U4.11 (C)
unnamed: U4.8 (~Q), U4.12 (D)
unnamed: U3.6, U4.10 (~S)
unnamed: C54.1, JP1.1, U13.3 (OUT)

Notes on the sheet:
Support Circuitry
Indicators/Headers
STANDBY LED
-5V Regulator
Terminating Resistors
Mounting Holes
Power/Fans
Filter Caps

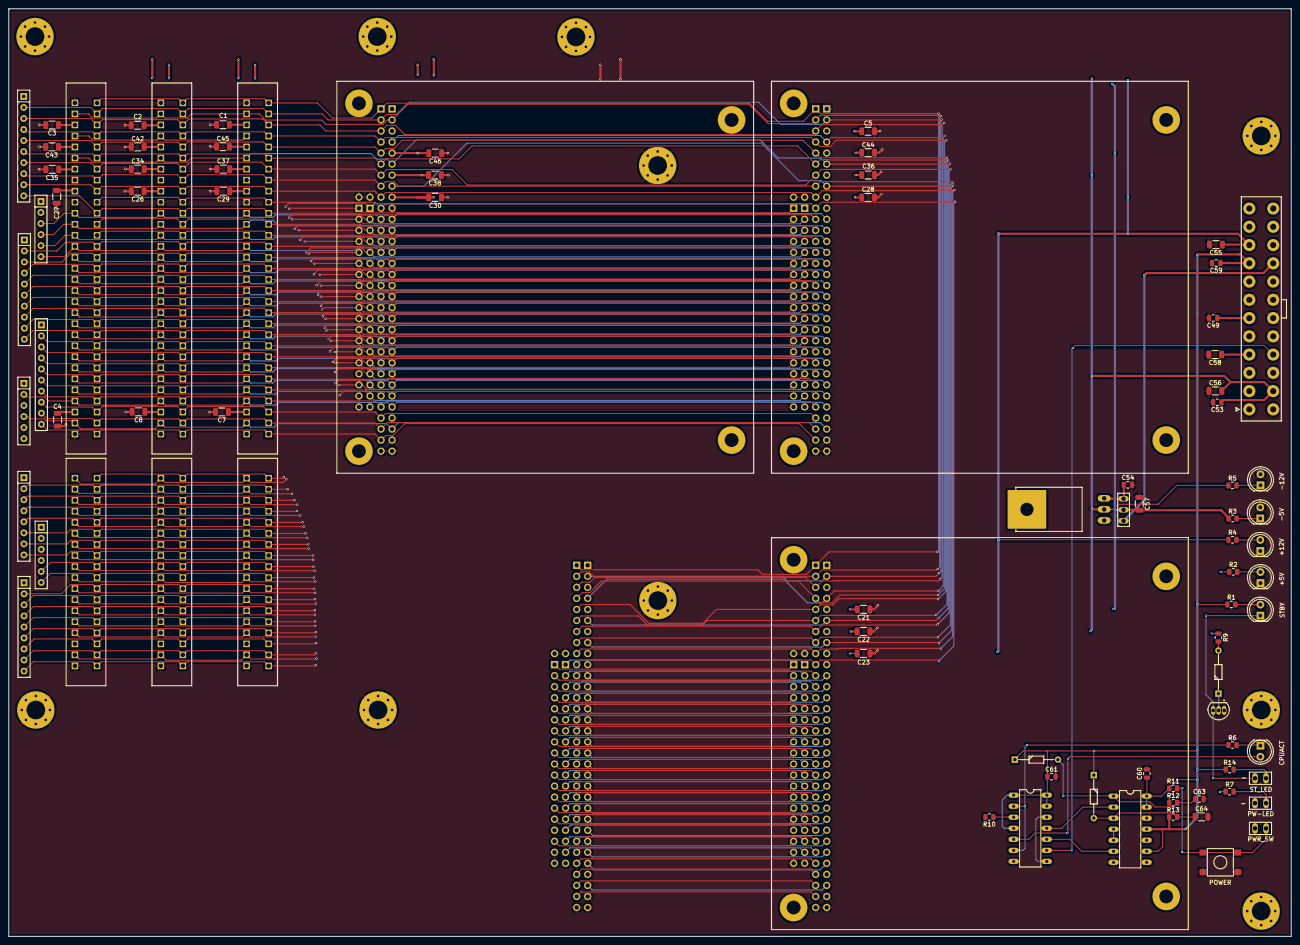
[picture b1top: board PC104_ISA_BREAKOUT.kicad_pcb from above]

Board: 4 copper layers, 295.0 x 213.4 mm, 94 parts (0 on the bottom side), 119 nets.

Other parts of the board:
H2#2: H_HOLE; MountingHole_4.3mm_M4_Pad_Via

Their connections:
GND: H2#2.1; also elsewhere on the board

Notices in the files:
PC104+Proto/PC104+Proto.kicad_pcb:
PC104+PROTO Rev1.0 (c)2025 Paula Maddox github.com/TechPaula
PC104Gus/hw/PC104GUS.kicad_pcb:
© 2023 Ian Scott aka polpo
licensed under CERN-OHL-P v2
